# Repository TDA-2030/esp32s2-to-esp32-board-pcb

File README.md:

# esp32s2-to-esp32-board-pcb

A board for converting ESP32-S2-Saola-1 to ESP32-DevKitC

## Picture

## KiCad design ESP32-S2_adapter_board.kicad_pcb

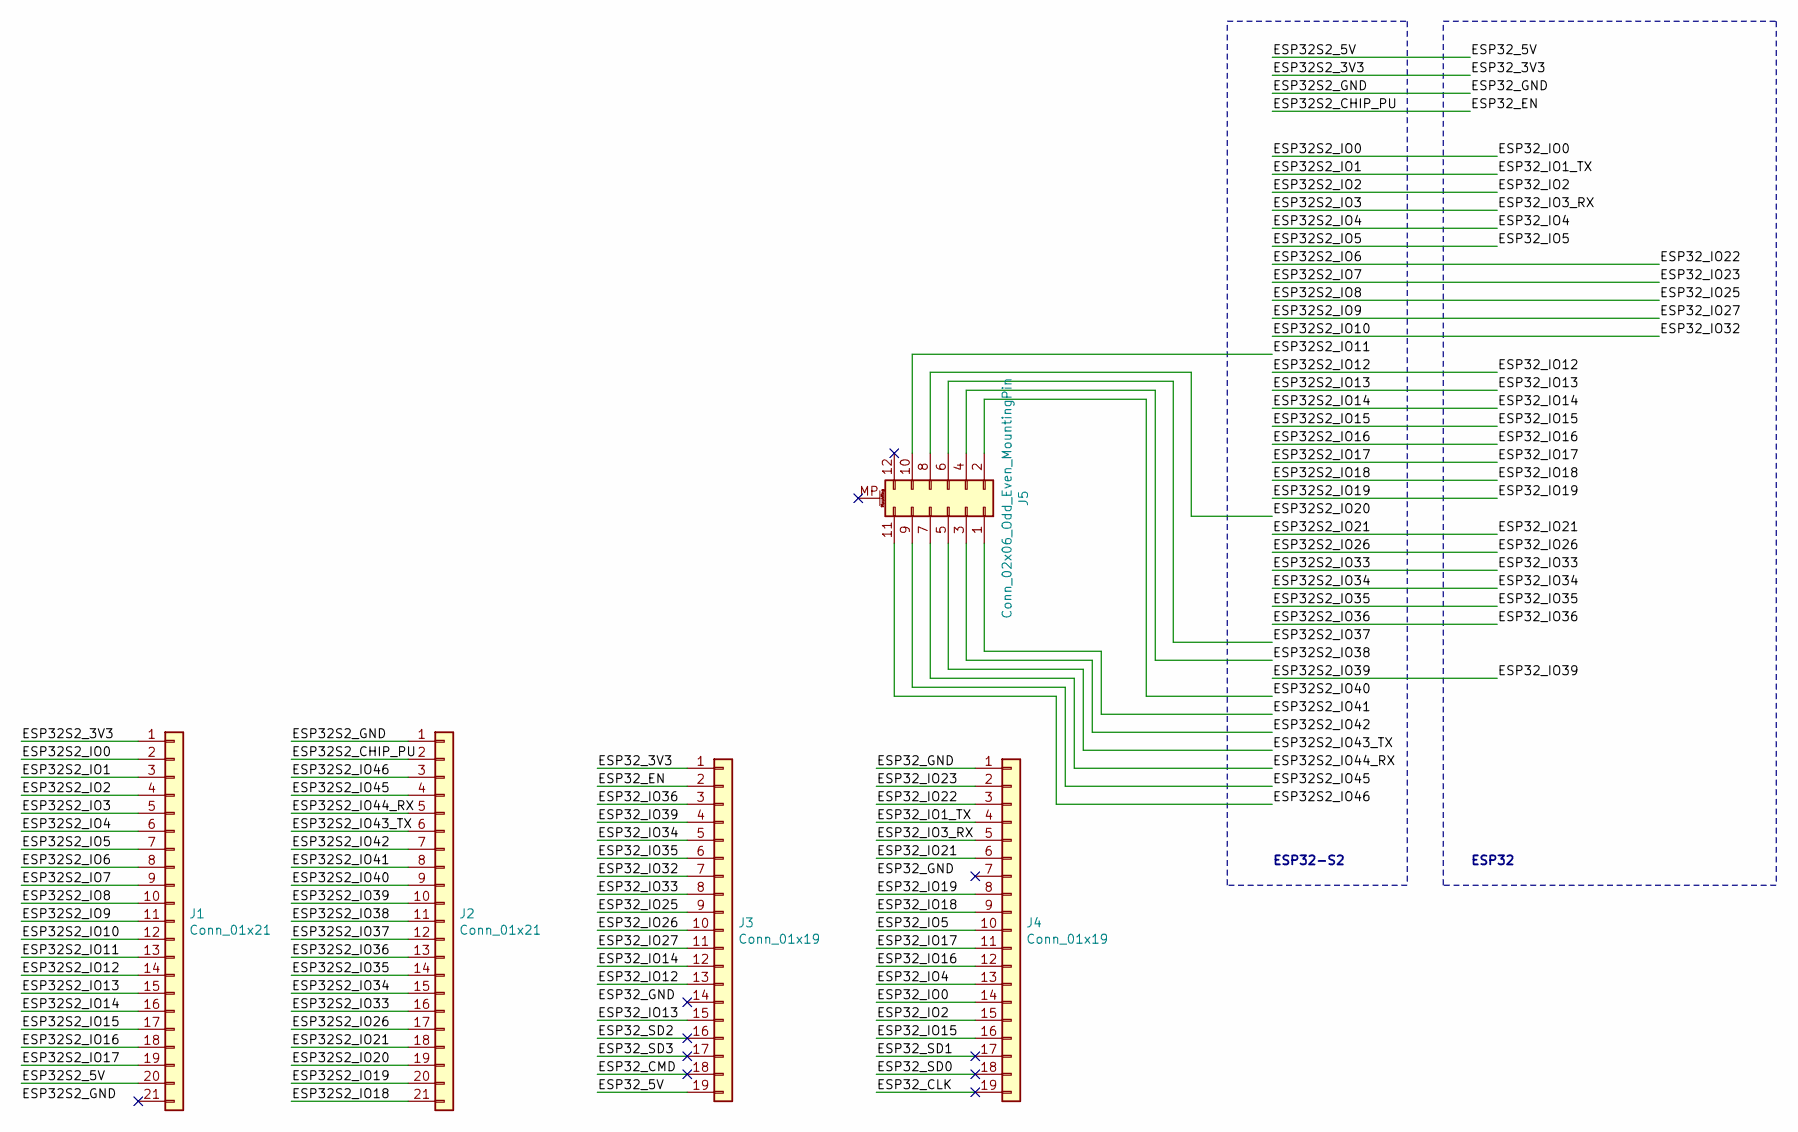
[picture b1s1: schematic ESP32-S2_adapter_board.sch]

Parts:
J1, J2: Conn_01x21; PinHeader_1x21_P2.54mm_Vertical
J3, J4: Conn_01x19; PinHeader_1x19_P2.54mm_Vertical
J5: Conn_02x06_Odd_Even_MountingPin; PinHeader_2x06_P2.54mm_Horizontal

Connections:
/ESP32S2_3V3: J1.1, J3.1
/ESP32S2_5V: J1.20, J3.19
/ESP32S2_CHIP_PU: J2.2, J3.2
/ESP32S2_GND: J2.1, J4.1
/ESP32S2_IO0: J1.2, J4.14
/ESP32S2_IO1: J1.3, J4.4
/ESP32S2_IO2: J1.4, J4.15
/ESP32S2_IO3: J1.5, J4.5
/ESP32S2_IO4: J1.6, J4.13
/ESP32S2_IO5: J1.7, J4.10
/ESP32S2_IO6: J1.8, J4.3
/ESP32S2_IO7: J1.9, J4.2
/ESP32S2_IO8: J1.10, J3.9
/ESP32S2_IO9: J1.11, J3.11
/ESP32S2_IO10: J1.12, J3.7
/ESP32S2_IO11: J1.13, J5.10
/ESP32S2_IO12: J1.14, J3.13
/ESP32S2_IO13: J1.15, J3.15
/ESP32S2_IO14: J1.16, J3.12
/ESP32S2_IO15: J1.17, J4.16
/ESP32S2_IO16: J1.18, J4.12
/ESP32S2_IO17: J1.19, J4.11
/ESP32S2_IO18: J2.21, J4.9
/ESP32S2_IO19: J2.20, J4.8
/ESP32S2_IO20: J2.19, J5.8
/ESP32S2_IO21: J2.18, J4.6
/ESP32S2_IO26: J2.17, J3.10
/ESP32S2_IO33: J2.16, J3.8
/ESP32S2_IO34: J2.15, J3.5
/ESP32S2_IO35: J2.14, J3.6
/ESP32S2_IO36: J2.13, J3.3
/ESP32S2_IO37: J2.12, J5.6
/ESP32S2_IO38: J2.11, J5.4
/ESP32S2_IO39: J2.10, J3.4
/ESP32S2_IO40: J2.9, J5.2
/ESP32S2_IO41: J2.8, J5.1
/ESP32S2_IO42: J2.7, J5.3
/ESP32S2_IO43_TX: J2.6, J5.5
/ESP32S2_IO44_RX: J2.5, J5.7
/ESP32S2_IO45: J2.4, J5.9
/ESP32S2_IO46: J2.3, J5.11
/ESP32_CLK: J4.19
/ESP32_CMD: J3.18
/ESP32_SD0: J4.18
/ESP32_SD1: J4.17
/ESP32_SD2: J3.16
/ESP32_SD3: J3.17

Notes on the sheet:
ESP32-S2
ESP32

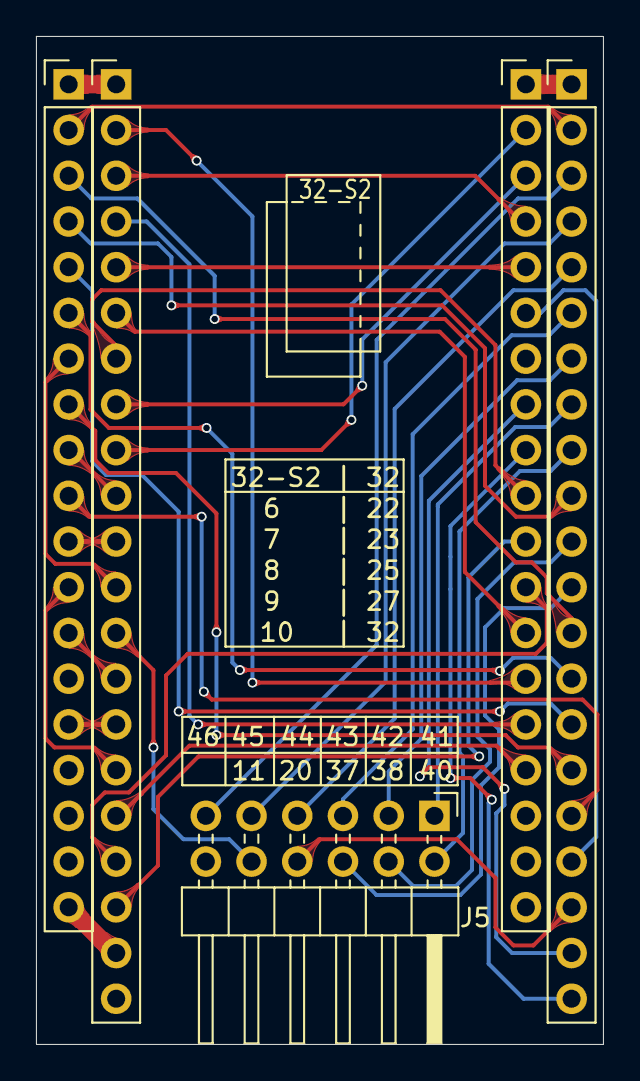
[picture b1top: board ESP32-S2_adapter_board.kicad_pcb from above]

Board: 2 copper layers, 31.5 x 56.0 mm, 5 parts (0 on the bottom side), 41 nets.

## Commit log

2020-09-13 add pcb design files
2020-09-21 feat: add gerber files
